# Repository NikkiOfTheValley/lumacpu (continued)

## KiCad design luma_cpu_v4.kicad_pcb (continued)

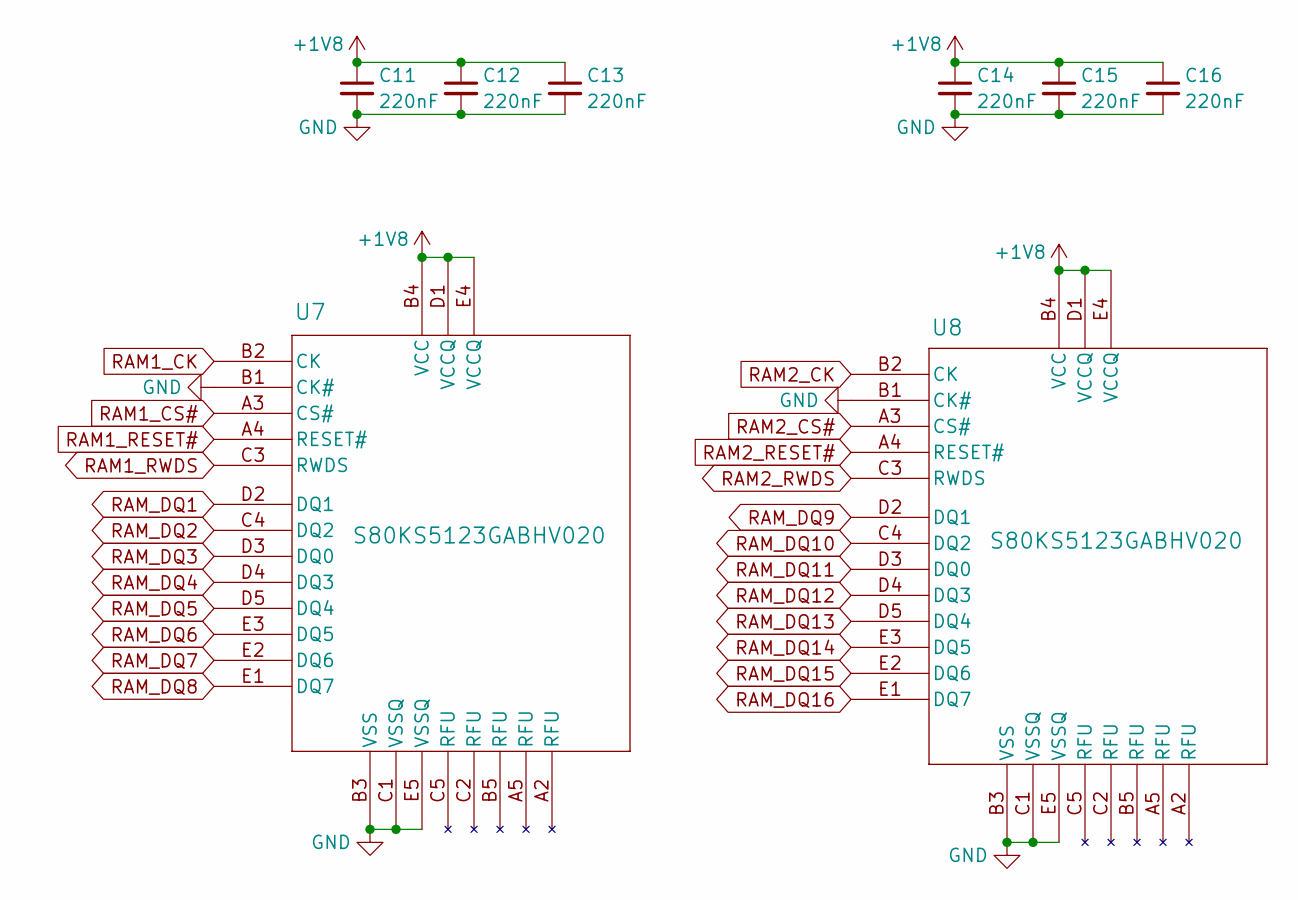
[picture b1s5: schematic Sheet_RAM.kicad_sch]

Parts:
C11, C12, C13, C14, C15, C16: 220nF; C_0201_0603Metric_Pad0.64x0.40mm_HandSolder
U7, U8: S80KS5123GABHV020; PG-BGA-24-801

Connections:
+1V8: C11.1, C12.1, C13.1, C14.1, C15.1, C16.1, U7.B4 (VCC), U7.D1 (VCCQ), U7.E4 (VCCQ), U8.B4 (VCC), U8.D1 (VCCQ), U8.E4 (VCCQ); also elsewhere on the board
GND: C11.2, C12.2, C13.2, C14.2, C15.2, C16.2, U7.B1 (CK#), U7.B3 (VSS), U7.C1 (VSSQ), U7.E5 (VSSQ), U8.B1 (CK#), U8.B3 (VSS), U8.C1 (VSSQ), U8.E5 (VSSQ); also elsewhere on the board
RAM1_CK: U7.B2 (CK); also elsewhere on the board
RAM1_CS#: U7.A3 (CS#); also elsewhere on the board
RAM1_RESET#: U7.A4 (RESET#); also elsewhere on the board
RAM1_RWDS: U7.C3 (RWDS); also elsewhere on the board
RAM2_CK: U8.B2 (CK); also elsewhere on the board
RAM2_CS#: U8.A3 (CS#); also elsewhere on the board
RAM2_RESET#: U8.A4 (RESET#); also elsewhere on the board
RAM2_RWDS: U8.C3 (RWDS); also elsewhere on the board
RAM_DQ1: U7.D2 (DQ1); also elsewhere on the board
RAM_DQ2: U7.C4 (DQ2); also elsewhere on the board
RAM_DQ3: U7.D3 (DQ0); also elsewhere on the board
RAM_DQ4: U7.D4 (DQ3); also elsewhere on the board
RAM_DQ5: U7.D5 (DQ4); also elsewhere on the board
RAM_DQ6: U7.E3 (DQ5); also elsewhere on the board
RAM_DQ7: U7.E2 (DQ6); also elsewhere on the board
RAM_DQ8: U7.E1 (DQ7); also elsewhere on the board
RAM_DQ9: U8.D2 (DQ1); also elsewhere on the board
RAM_DQ10: U8.C4 (DQ2); also elsewhere on the board
RAM_DQ11: U8.D3 (DQ0); also elsewhere on the board
RAM_DQ12: U8.D4 (DQ3); also elsewhere on the board
RAM_DQ13: U8.D5 (DQ4); also elsewhere on the board
RAM_DQ14: U8.E3 (DQ5); also elsewhere on the board
RAM_DQ15: U8.E2 (DQ6); also elsewhere on the board
RAM_DQ16: U8.E1 (DQ7); also elsewhere on the board

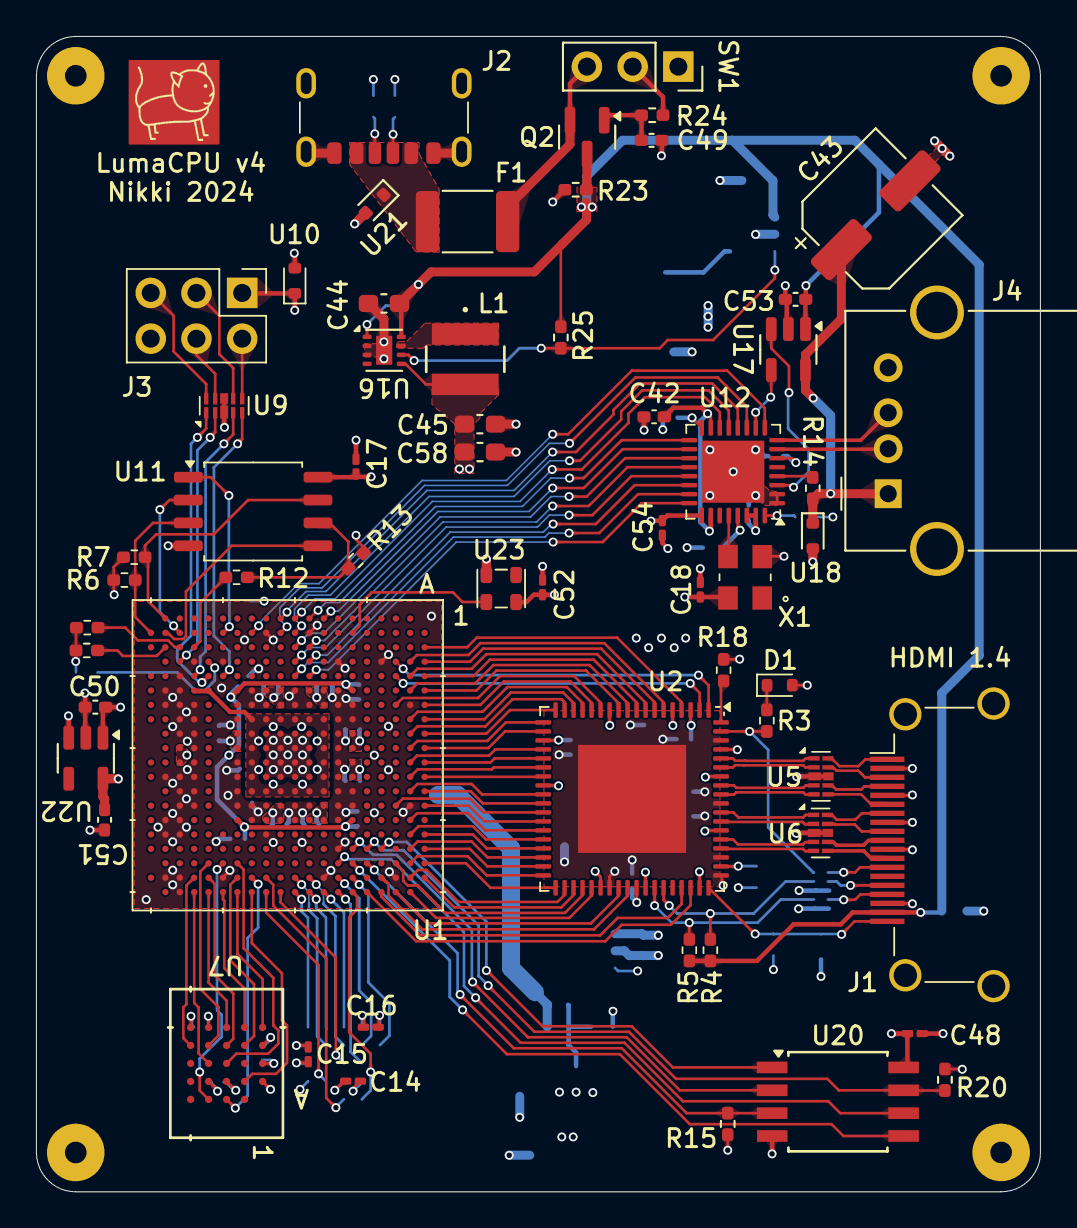
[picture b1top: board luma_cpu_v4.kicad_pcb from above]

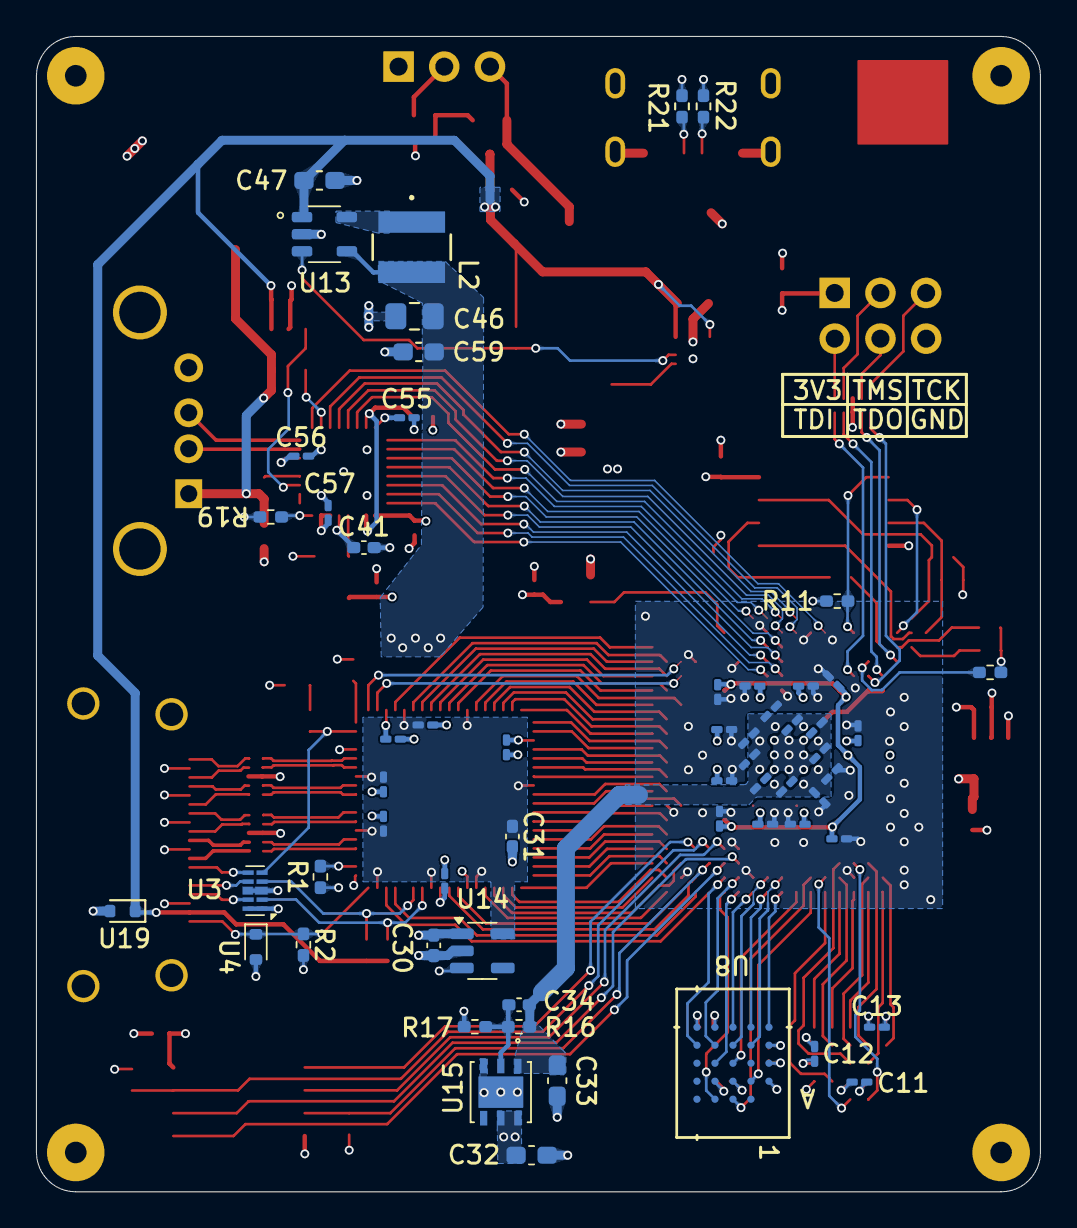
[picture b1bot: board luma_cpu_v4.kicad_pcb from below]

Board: 4 copper layers, 55.8 x 64.2 mm, 122 parts (59 on the bottom side), 155 nets.

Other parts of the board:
C1: 220nF; C_0201_0603Metric_Pad0.64x0.40mm_HandSolder

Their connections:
+1V1: C1.1; also elsewhere on the board
GND: C1.2; also elsewhere on the board

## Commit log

2024-12-22 Added KiCAD project files
2024-12-22 updated BOM to make sense
2024-12-22 added some capacitors to various components that weren't capacitored enough
2024-12-23 fixed some silkscreen thickness issues
